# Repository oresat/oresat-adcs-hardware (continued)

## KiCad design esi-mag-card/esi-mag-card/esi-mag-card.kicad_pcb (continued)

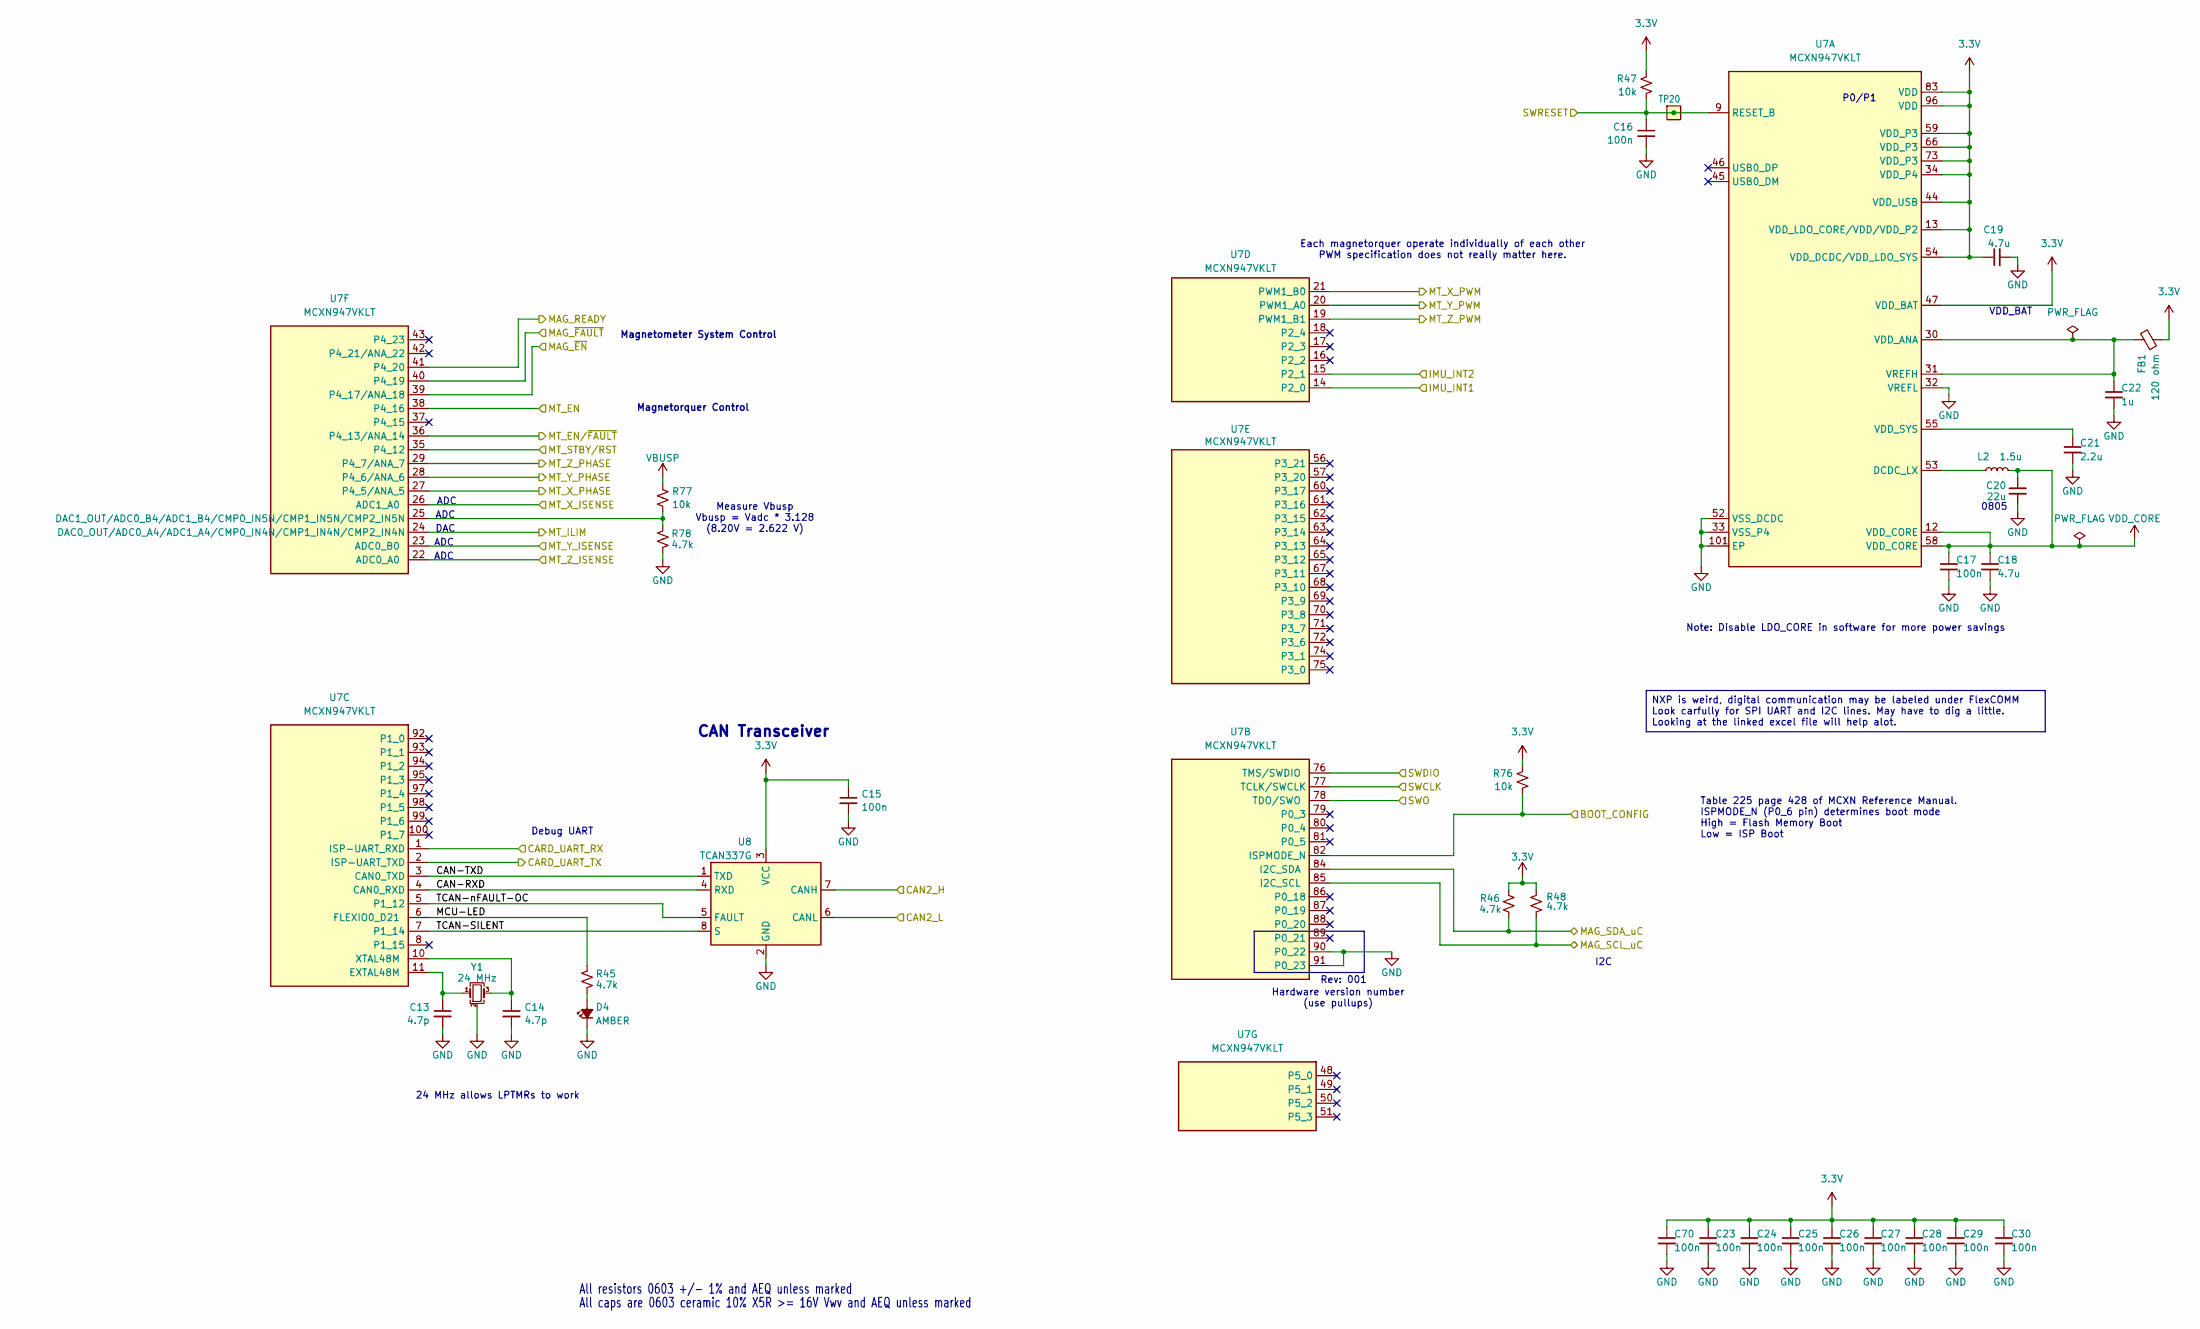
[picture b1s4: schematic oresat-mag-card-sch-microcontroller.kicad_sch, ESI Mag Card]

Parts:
C13, C14: 4.7p; 0603-C-NOSILK; MPN C0603C479D5GACAUTO
C15, C16, C17, C23, C24, C25, C26, C27, C28, C29, C30, C70: 100n; 0603-C-NOSILK; MPN C0603C104K5RACAUTO
C18, C19: 4.7u; 0603-C-NOSILK; MPN GRT188C71C475KE13D
C20: 22u; 0805-B-NOSILK; MPN GRT21BC81C226ME13L
C21: 2.2u; 0603-C-NOSILK; MPN GRT188C71E225KE13D
C22: 1u; 0603-C-NOSILK; MPN GRT188R71E105KE13D
D4: AMBER; LED_0603_1608Metric; MPN 150060AS75000
FB1: 120 ohm; 0805-B-NOSILK; MPN 2508051217Y6
L2: 1.5u; L_0805_2012Metric; MPN SRP2012TMA-1R5M
R45, R46, R48, R78: 4.7k; 0603-C-NOSILK; MPN RMCF0603FT4K70
R47, R76, R77: 10k; 0603-C-NOSILK; MPN RMCF0603FT10K0
TP20: Test-Point; TestPoint-0.75mm-th
U7: MCXN947VKLT; MCXN947KVLT-QFP50P1600X1600X160-101N; MPN MCXN947VKLT
U8: TCAN337G; SOT-23-8; MPN TCAN337GDCNR
Y1: 24 MHz; Crystal_SMD_2016-4Pin_2.0x1.6mm; MPN 830108212309

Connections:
3.3V: C15.1, C19.1, C23.1, C24.1, C25.1, C26.1, C27.1, C28.1, C29.1, C30.1, C70.1, FB1.1, R46.2, R47.2, R48.2, R76.2, U7.13 (VDD_LDO_CORE/VDD/VDD_P2), U7.34 (VDD_P4), U7.44 (VDD_USB), U7.47 (VDD_BAT), U7.54 (VDD_DCDC/VDD_LDO_SYS), U7.59 (VDD_P3), U7.66 (VDD_P3), U7.73 (VDD_P3), U7.83 (VDD), U7.96 (VDD), U8.3 (VCC); also elsewhere on the board
/CAN2_H: U8.7 (CANH); also elsewhere on the board
/CAN2_L: U8.6 (CANL); also elsewhere on the board
/Card Power Domain/BOOT_CONFIG: R76.1, U7.82 (ISPMODE_N); also elsewhere on the board
/Card Power Domain/CARD-UART-RX: U7.1 (ISP-UART_RXD); also elsewhere on the board
/Card Power Domain/CARD-UART-TX: U7.2 (ISP-UART_TXD); also elsewhere on the board
/Magnetometers + IMU/IMU_INT1: U7.14 (P2_0); also elsewhere on the board
/Magnetometers + IMU/IMU_INT2: U7.15 (P2_1); also elsewhere on the board
/Magnetometers + IMU/MAG_READY: U7.41 (P4_20); also elsewhere on the board
/Magnetometers + IMU/MAG_SCL_uC: R48.1, U7.85 (I2C_SCL); also elsewhere on the board
/Magnetometers + IMU/MAG_SDA_uC: R46.1, U7.84 (I2C_SDA); also elsewhere on the board
/Magnetometers + IMU/MAG_~EN: U7.39 (P4_17/ANA_18); also elsewhere on the board
/Magnetometers + IMU/MAG_~FAULT: U7.40 (P4_19); also elsewhere on the board
/Magnetorquers/MT_EN: U7.38 (P4_16); also elsewhere on the board
/Magnetorquers/MT_EN/~FAULT: U7.36 (P4_13/ANA_14); also elsewhere on the board
/Magnetorquers/MT_ILIM: U7.24 (DAC0_OUT/ADC0_A4/ADC1_A4/CMP0_IN4N/CMP1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); also elsewhere on the board
/Magnetorquers/MT_STBY/RST: U7.35 (P4_12); also elsewhere on the board
/Magnetorquers/MT_X_ISENSE: U7.26 (ADC1_A0); also elsewhere on the board
/Magnetorquers/MT_X_PHASE: U7.27 (P4_5/ANA_5); also elsewhere on the board
/Magnetorquers/MT_X_PWM: U7.21 (PWM1_B0); also elsewhere on the board
/Magnetorquers/MT_Y_ISENSE: U7.23 (ADC0_B0); also elsewhere on the board
/Magnetorquers/MT_Y_PHASE: U7.28 (P4_6/ANA_6); also elsewhere on the board
/Magnetorquers/MT_Y_PWM: U7.20 (PWM1_A0); also elsewhere on the board
/Magnetorquers/MT_Z_ISENSE: U7.22 (ADC0_A0); also elsewhere on the board
/Magnetorquers/MT_Z_PHASE: U7.29 (P4_7/ANA_7); also elsewhere on the board
/Magnetorquers/MT_Z_PWM: U7.19 (PWM1_B1); also elsewhere on the board
/Microcontroller/CAN-RXD: U7.4 (CAN0_RXD), U8.4 (RXD)
/Microcontroller/CAN-TXD: U7.3 (CAN0_TXD), U8.1 (TXD)
/Microcontroller/MCU-LED: R45.1, U7.6 (FLEXIO0_D21)
/Microcontroller/TCAN-SILENT: U7.7 (P1_14), U8.8 (S)
/Microcontroller/TCAN-nFAULT-OC: U7.5 (P1_12), U8.5 (FAULT)
/NRST: C16.1, R47.1, TP20.1 (1_1), U7.9 (RESET_B); also elsewhere on the board
/SWCLK: U7.77 (TCLK/SWCLK); also elsewhere on the board
/SWDIO: U7.76 (TMS/SWDIO); also elsewhere on the board
/SWO: U7.78 (TDO/SWO); also elsewhere on the board
GND: C13.2, C14.2, C15.2, C16.2, C17.2, C18.2, C19.2, C20.2, C21.2, C22.2, C23.2, C24.2, C25.2, C26.2, C27.2, C28.2, C29.2, C30.2, C70.2, D4.1 (K), R78.2, U7.32 (VREFL), U7.33 (VSS_P4), U7.52 (VSS_DCDC), U7.90 (P0_22), U7.91 (P0_23), U7.101 (EP), U8.2 (GND), Y1.2 (G), Y1.4 (G); also elsewhere on the board
unnamed: D4.2 (A), R45.2
unnamed: L2.2, U7.53 (DCDC_LX)
unnamed: C22.1, FB1.2, U7.30 (VDD_ANA), U7.31 (VREFH)
unnamed: C21.1, U7.55 (VDD_SYS)
unnamed: C14.1, U7.10 (XTAL48M), Y1.3
unnamed: C13.1, U7.11 (EXTAL48M), Y1.1
unnamed: R77.1, R78.1, U7.25 (DAC1_OUT/ADC0_B4/ADC1_B4/CMP0_IN5N/CMP1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)
VBUSP: R77.2; also elsewhere on the board
VDD_CORE: C17.1, C18.1, C20.1, L2.1, U7.12 (VDD_CORE), U7.58 (VDD_CORE)

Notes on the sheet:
Magnetometer System Control
Measure Vbusp Vbusp = Vadc * 3.128 (8.20V = 2.622 V)
Hardware version number (use pullups)
ADC
Magnetorquer Control
Each magnetorquer operate individually of each other PWM specification does not really matter here.
Debug UART
Note: Disable LDO_CORE in software for more power savings
0805
All resistors 0603 +/- 1% and AEQ unless marked
I2C
VDD_BAT
Table 225 page 428 of MCXN Reference Manual. ISPMODE_N (P0_6 pin) determines boot mode High = Flash Memory Boot Low = ISP Boot
CAN Transceiver
All caps are 0603 ceramic 10% X5R >= 16V Vwv and AEQ unless marked
24 MHz allows LPTMRs to work
P0/P1
DAC
Rev: 001
NXP is weird, digital communication may be labeled under FlexCOMM Look carfully for SPI UART and I2C lines. May have to dig a little. Looking at the linked excel file will help alot.

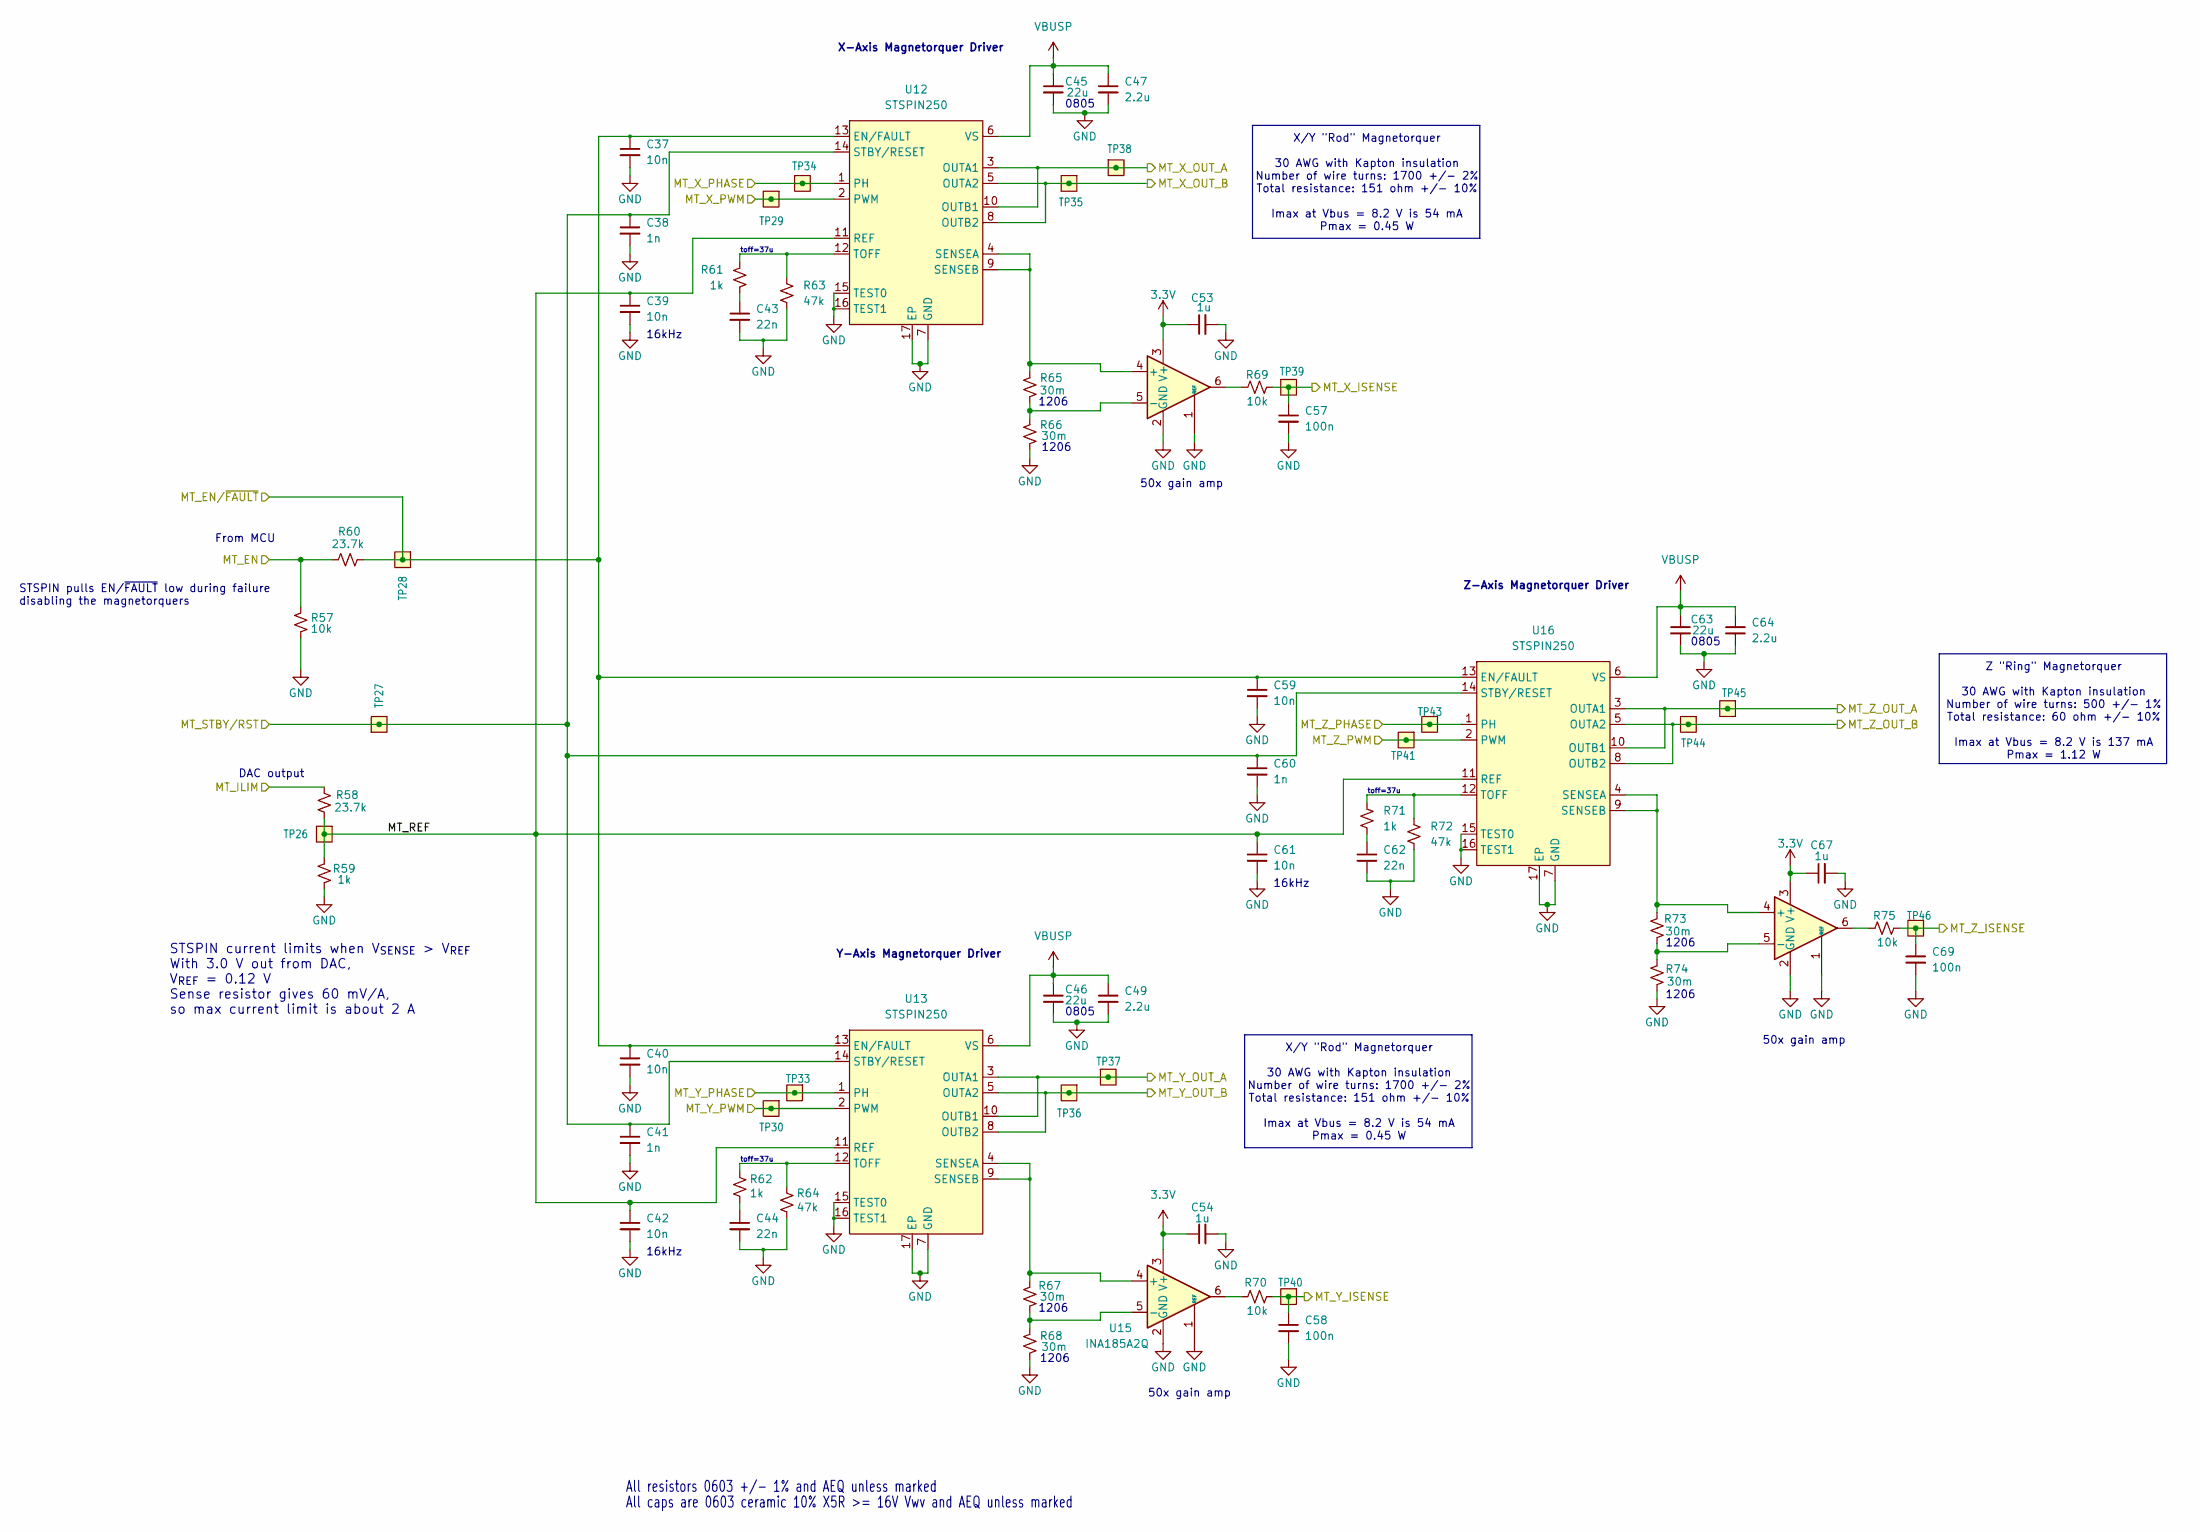
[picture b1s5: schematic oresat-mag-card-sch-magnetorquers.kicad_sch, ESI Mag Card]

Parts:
C37, C39, C40, C42, C59, C61: 10n; 0603-C-NOSILK; MPN C0603C103J5RACAUTO
C38, C41, C60: 1n; 0603-C-NOSILK; MPN C0603C102J5RACAUTO
C43, C44, C62: 22n; 0603-C-NOSILK; MPN C0603C223J5RACAUTO
C45, C46, C63: 22u; 0805-B-NOSILK; MPN GRT21BC81C226ME13L
C47, C49, C64: 2.2u; 0603-C-NOSILK; MPN GRT188C71E225KE13D
C53, C54, C67: 1u; 0603-C-NOSILK; MPN GRT188R71E105KE13D
C57, C58, C69: 100n; 0603-C-NOSILK; MPN C0603C104K5RACAUTO
R57, R69, R70, R75: 10k; 0603-C-NOSILK; MPN RMCF0603FT10K0
R58, R60: 23.7k; 0603-C-NOSILK; MPN RMCF0603FT23K7
R59, R61, R62, R71: 1k; 0603-C-NOSILK; MPN RMCF0603FT1K00
R63, R64, R72: 47k; 0603-C-NOSILK; MPN RMCF0603FT47K0
R65, R66, R67, R68, R73, R74: 30m; 1206-C; MPN CSR1206FK30L0
TP26, TP27, TP28, TP29, TP30, TP33, TP34, TP35, TP36, TP37, TP38, TP39, TP40, TP41, TP43, TP44, TP45, TP46: Test-Point; TestPoint-0.75mm-th
U12, U13, U16: STSPIN250; VQFN-16-1EP_3x3mm_P0.5mm_EP1.8x1.8mm; MPN STSPIN250
U14, U15, U17: INA185A2Q; SOT-363_SC-70-6; MPN INA185A2QDCKRQ1

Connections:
3.3V: C53.1, C54.1, C67.1, U14.3 (V+), U15.3 (V+), U17.3 (V+); also elsewhere on the board
/MT_X_OUT_A: TP38.1 (1_1), U12.3 (OUTA1), U12.10 (OUTB1); also elsewhere on the board
/MT_X_OUT_B: TP35.1 (1_1), U12.5 (OUTA2), U12.8 (OUTB2); also elsewhere on the board
/MT_Y_OUT_A: TP37.1 (1_1), U13.3 (OUTA1), U13.10 (OUTB1); also elsewhere on the board
/MT_Y_OUT_B: TP36.1 (1_1), U13.5 (OUTA2), U13.8 (OUTB2); also elsewhere on the board
/MT_Z_OUT_A: TP45.1 (1_1), U16.3 (OUTA1), U16.10 (OUTB1); also elsewhere on the board
/MT_Z_OUT_B: TP44.1 (1_1), U16.5 (OUTA2), U16.8 (OUTB2); also elsewhere on the board
/Magnetorquers/MT_EN: R57.2, R60.1; also elsewhere on the board
/Magnetorquers/MT_EN/~FAULT: C37.1, C40.1, C59.1, R60.2, TP28.1 (1_1), U12.13 (EN/FAULT), U13.13 (EN/FAULT), U16.13 (EN/FAULT); also elsewhere on the board
/Magnetorquers/MT_ILIM: R58.2; also elsewhere on the board
/Magnetorquers/MT_REF: C39.1, C42.1, C61.1, R58.1, R59.2, TP26.1 (1_1), U12.11 (REF), U13.11 (REF), U16.11 (REF)
/Magnetorquers/MT_STBY/RST: C38.1, C41.1, C60.1, TP27.1 (1_1), U12.14 (STBY/RESET), U13.14 (STBY/RESET), U16.14 (STBY/RESET); also elsewhere on the board
/Magnetorquers/MT_X_ISENSE: C57.1, R69.2, TP39.1 (1_1); also elsewhere on the board
/Magnetorquers/MT_X_PHASE: TP34.1 (1_1), U12.1 (PH); also elsewhere on the board
/Magnetorquers/MT_X_PWM: TP29.1 (1_1), U12.2 (PWM); also elsewhere on the board
/Magnetorquers/MT_Y_ISENSE: C58.1, R70.2, TP40.1 (1_1); also elsewhere on the board
/Magnetorquers/MT_Y_PHASE: TP33.1 (1_1), U13.1 (PH); also elsewhere on the board
/Magnetorquers/MT_Y_PWM: TP30.1 (1_1), U13.2 (PWM); also elsewhere on the board
/Magnetorquers/MT_Z_ISENSE: C69.1, R75.2, TP46.1 (1_1); also elsewhere on the board
/Magnetorquers/MT_Z_PHASE: TP43.1 (1_1), U16.1 (PH); also elsewhere on the board
/Magnetorquers/MT_Z_PWM: TP41.1 (1_1), U16.2 (PWM); also elsewhere on the board
GND: C37.2, C38.2, C39.2, C40.2, C41.2, C42.2, C43.2, C44.2, C45.2, C46.2, C47.2, C49.2, C53.2, C54.2, C57.2, C58.2, C59.2, C60.2, C61.2, C62.2, C63.2, C64.2, C67.2, C69.2, R57.1, R59.1, R63.2, R64.2, R66.1, R68.1, R72.2, R74.1, U12.7 (GND), U12.15 (TEST0), U12.16 (TEST1), U12.17 (EP), U13.7 (GND), U13.15 (TEST0), U13.16 (TEST1), U13.17 (EP), U14.1 (REF), U14.2 (GND), U15.1 (REF), U15.2 (GND), U16.7 (GND), U16.15 (TEST0), U16.16 (TEST1), U16.17 (EP), U17.1 (REF), U17.2 (GND); also elsewhere on the board
unnamed: C43.1, R61.2
unnamed: C44.1, R62.2
unnamed: C62.1, R71.2
unnamed: R69.1, U14.6
unnamed: R70.1, U15.6
unnamed: R75.1, U17.6
unnamed: R65.2, U12.4 (SENSEA), U12.9 (SENSEB), U14.4 (+)
unnamed: R61.1, R63.1, U12.12 (TOFF)
unnamed: R67.2, U13.4 (SENSEA), U13.9 (SENSEB), U15.4 (+)
unnamed: R62.1, R64.1, U13.12 (TOFF)
unnamed: R65.1, R66.2, U14.5 (-)
unnamed: R67.1, R68.2, U15.5 (-)
unnamed: R73.2, U16.4 (SENSEA), U16.9 (SENSEB), U17.4 (+)
unnamed: R71.1, R72.1, U16.12 (TOFF)
unnamed: R73.1, R74.2, U17.5 (-)
VBUSP: C45.1, C46.1, C47.1, C49.1, C63.1, C64.1, U12.6 (VS), U13.6 (VS), U16.6 (VS); also elsewhere on the board

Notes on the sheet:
1206
STSPIN current limits when V_{SENSE} > V_{REF} With 3.0 V out from DAC, V_{REF} = 0.12 V Sense resistor gives 60 mV/A, so max current limit is about 2 A
DAC output
16kHz
50x gain amp
toff=37u
Y-Axis Magnetorquer Driver
X/Y "Rod" Magnetorquer 30 AWG with Kapton insulation Number of wire turns: 1700 +/- 2% Total resistance: 151 ohm +/- 10% Imax at Vbus = 8.2 V is 54 mA Pmax = 0.45 W
From MCU
All caps are 0603 ceramic 10% X5R >= 16V Vwv and AEQ unless marked
Z "Ring" Magnetorquer 30 AWG with Kapton insulation Number of wire turns: 500 +/- 1% Total resistance: 60 ohm +/- 10% Imax at Vbus = 8.2 V is 137 mA Pmax = 1.12 W
0805
STSPIN pulls EN/~{FAULT} low during failure disabling the magnetorquers
All resistors 0603 +/- 1% and AEQ unless marked
Z-Axis Magnetorquer Driver
X-Axis Magnetorquer Driver

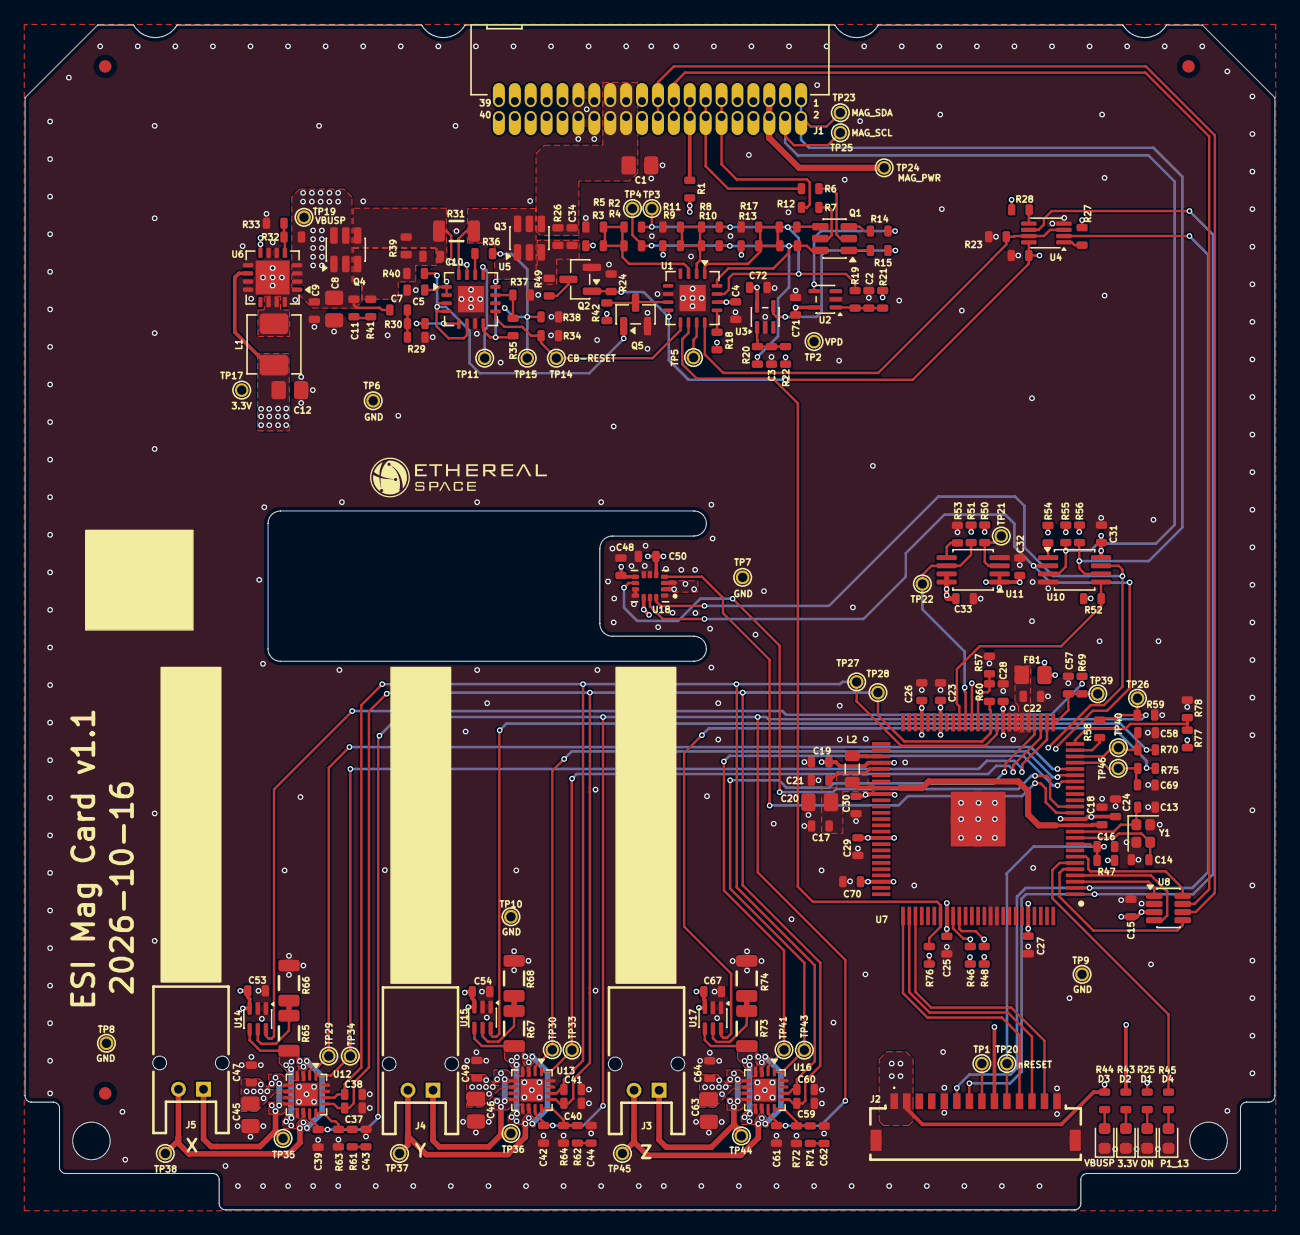
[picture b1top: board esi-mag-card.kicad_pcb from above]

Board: 4 copper layers, 99.8 x 94.6 mm, 219 parts (0 on the bottom side), 120 nets.

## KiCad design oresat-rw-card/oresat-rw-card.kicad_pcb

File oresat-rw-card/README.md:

---
title: "**OreSat Reaction Wheel (RW) Card**"
subtitle: |
  **Fabrication and Assembly Information**\
  For build TIME-STAMP
fontsize: 10pt
geometry:
  - margin=0.5in
toc: true
toc-depth: 2
colorlinks: true
urlcolor: blue
---

\newpage

# About this Board

## Board Description

The OreSat RW Card run the four reaction wheels on the open source [OreSat CubeSat system](https://www.oresat.org/). The RW card:

- Has an OreSat Power Domain (OPD) per reaction wheel.
- Requires a flexible cable between the card and the RW board.

## Documentation Links

- RW card hardware Git repository: <https://github.com/oresat/oresat-adcs-hardware>
- **TODO:** RW card Design Notes + Design Review Notes

## Documentation Files

| Filename                        | Notes                                    |
| ------------------------------- | ---------------------------------------- |
| README.pdf                      | This README file                         |
| PROJECT-NAME-outline.dxf        | Board outline (with holes) in DXF format |
| PROJECT-NAME-pcba.step          | 3D model of PCBA (with components)       |
| PROJECT-NAME-render-bot.jpg     | Render of the top of the 3D model        |
| PROJECT-NAME-render-bot.jpg     | Render of the bottom of the 3D model     |
| PROJECT-NAME-schematic.pdf      | PDF of board schematics                  |

## Contact Information

- Website: <https://www.oresat.org/>
- Email: <oresat@pdx.edu>
- Instagram: @pdxaerospace

## Board Renders

{width=50%}
{width=50%}

\newpage

# Printed Circuit Board (PCB) Fabrication Information

## Board Info

- 4 layer board
- Bounding box is 99.8 x 94.6 mm (3.93 x 3.72 in)
- Board thickness is 1.59 mm (0.063 inch)

## Board Requirements

- Design Rules
    - Minimum Trace / Space design rules
       - Outer layers: 0.127 mm (5.0 mil) / 0.127 mm (5.0 mil)
       - Inner layers: 0.127 mm (5.0 mil) / 0.127 mm (5.0 mil)
    - Outer dimension router tolerance: +/- 0.254 mm (10.0 mil)
    - Hole placement tolerance: +/- 0.075 mm (3.0 mil)
    - Inner tab routed slot tolerance: +/- 0.254 mm (10.0 mil)
- Drills
   - Drill Positional Tolerance: 0.051 mm (2.0 mil)
   - Drill Size tolerance: +/- 0.064 mm (2.5 mil)
- Plated/Un-plated holes
  - There are 2 un-plated (NPT) holes
  - There are 664 plated through (PTH) holes
  - PTH minimum diameter: 0.254 mm (10 mil)
  - PTH minimum annulus: 0.102 mm (4 mil) radius
- Outline/Routing
  - Requires a 1.0 mm or smaller diameter routing bit
- Slots
  - There is one cutout.
- Cutouts
  - There are no cutouts
- There are 3 fiducials on the top layer and 3 fiducials on the bottom layer.
- Panel tabs ("mouse bites")
   - Card edges must be smooth; no mouse bites or other intrusions into the card outline.
   - If external mouse bites are required, minimize and customer will remove by hand before assembly.
- If not otherwise specified, build to IPC 6012 Class 2 or better.

## Materials

- No controlled impedance.
- Outer layers must be 1 oz Copper, inner layers can be 0.5 or 1.0 oz Copper.
- Isola FR408HR or material recommended.
- Board Surface treatment should be ENIG, althogh immersion Silver is acceptable.
- White silkscreen on top and bottom surface
- Taiyo PSR-4000 or equivalent soldermask on top and bottom, no requirements for color.

## Suggested Stack Up

| Layer         | Thickness           | Notes                                        |
|---------------|---------------------|----------------------------------------------|
| Top Copper    | 0.043 mm /  1.7 mil |  Layer 1 foil, 1 oz Cu after plating         |
| prepreg       | 0.200 mm /  7.9 mil |  Prepreg - Isola FR408HR 2113                |
| Layer 2       | 0.018 mm /  0.7 mil |  Layer 2 foil, 0.5 oz Cu                     |
| Core          | 0.991 mm /   39 mil |  Core Isola FR408HR                          |
| Layer 3       | 0.018 mm /  0.7 mil |  Layer 3 foil, 0.5 oz Cu                     |
| prepreg       | 0.200 mm /  7.9 mil |  Prepreg - Isola FR408HR 2113                |
| Bottom Copper | 0.043 mm /  1.7 mil |  Layer 4 foil, 1 oz copper after plating     |
| **Total Stackup** | **1.588 mm / 62.5 mil** |                                      |

## Array / Panel Information

- Coordinate with Contract Manufacturer (CM) for optimal size of this panel.
- If no feedback from CM, then produce single boards (no panel).

## Fabrication Files

### IPC-2581 File

| Filename                 | Notes                                   |
| ------------------------ | --------------------------------------- |
| PROJECT-NAME-ipc2581.xml | IPC-2581 board information file         |

### Legacy PCB Files

| Filename                      | Notes                                         |
| ------------------------------| --------------------------------------------- |
| PROJECT-NAME-Edge_Cuts.gbr    | RS274X file for the dimension (outline) layer |
| PROJECT-NAME-F_Silkscreen.gbr | RS274X file for the top silkscreen            |
| PROJECT-NAME-F_Mask.gbr       | RS274X file for the top soldermask            |
| PROJECT-NAME-F_Cu.gbr         | RS274X file for the top copper layer          |
| PROJECT-NAME-In1_Cu.gbr       | RS274X file for the layer 2 copper            |
| PROJECT-NAME-In2_Cu.gbr       | RS274X file for the layer 3 copper            |
| PROJECT-NAME-B_Cu.gbr         | RS274X file for the bottom copper layer       |
| PROJECT-NAME-B_Mask.gbr       | RS274X file for the bottom soldermask         |
| PROJECT-NAME-B_Silkscreen.gbr | RS274X file for the bottom silkscreen         |
| PROJECT-NAME-NPTH.drl         | Excellon file for non-plated through holes    |
| PROJECT-NAME-PTH.drl          | Excellon file for plated through holes        | 

\newpage

# Printed Circuit Board Assembly (PCBA) Information

## Assembly Info

- There are components on the top and bottom sides of the board.
- This PCBA is mostly surface mount (SMT) with a one through-hole (THT) components.

## Assembly Requirements

- Assemble to IPC Class 2 or better
- Bake components that are not moisture sealed to appropriate levels as required.
- Solder paste MUST be leaded.
- Aqueous flux and wash strongly preferred.
   - Clean to NASA Standard "Visibly Clean (VC)": No particles or residues are visible to the naked eye.
- No conformal coating.
- Ship in antistatic protective bag

## Component Specific Assembly Information

- No specific requirements.

## Assembly Files

### IPC-2581 File

| Filename                 | Notes                           |
| ------------------------ | ------------------------------- |
| PROJECT-NAME-ipc2581.xml | IPC-2581 board information file |

### Bill of Materials (BOM)

| Filename             | Description                            |
| -------------------- | -------------------------------------- |
| PROJECT-NAME-bom.csv | BOM in Comma Separated Variable format |

### Solder Paste Stencils

| Filename                 | Notes                                            |
| ------------------------ | ------------------------------------------------ |
| PROJECT-NAME-B_Paste.gbr | RS274X file for top/front solder paste stencil   |
| PROJECT-NAME-F_Paste.gbr | RS274X file for bottom/back solder paste stencil |

### Mounting/Placement Location

| Filename            | Description                                 |
| ------------------- | ------------------------------------------- |
| PROJECT-NAME-3u.pos | Pick and place locations for components     |

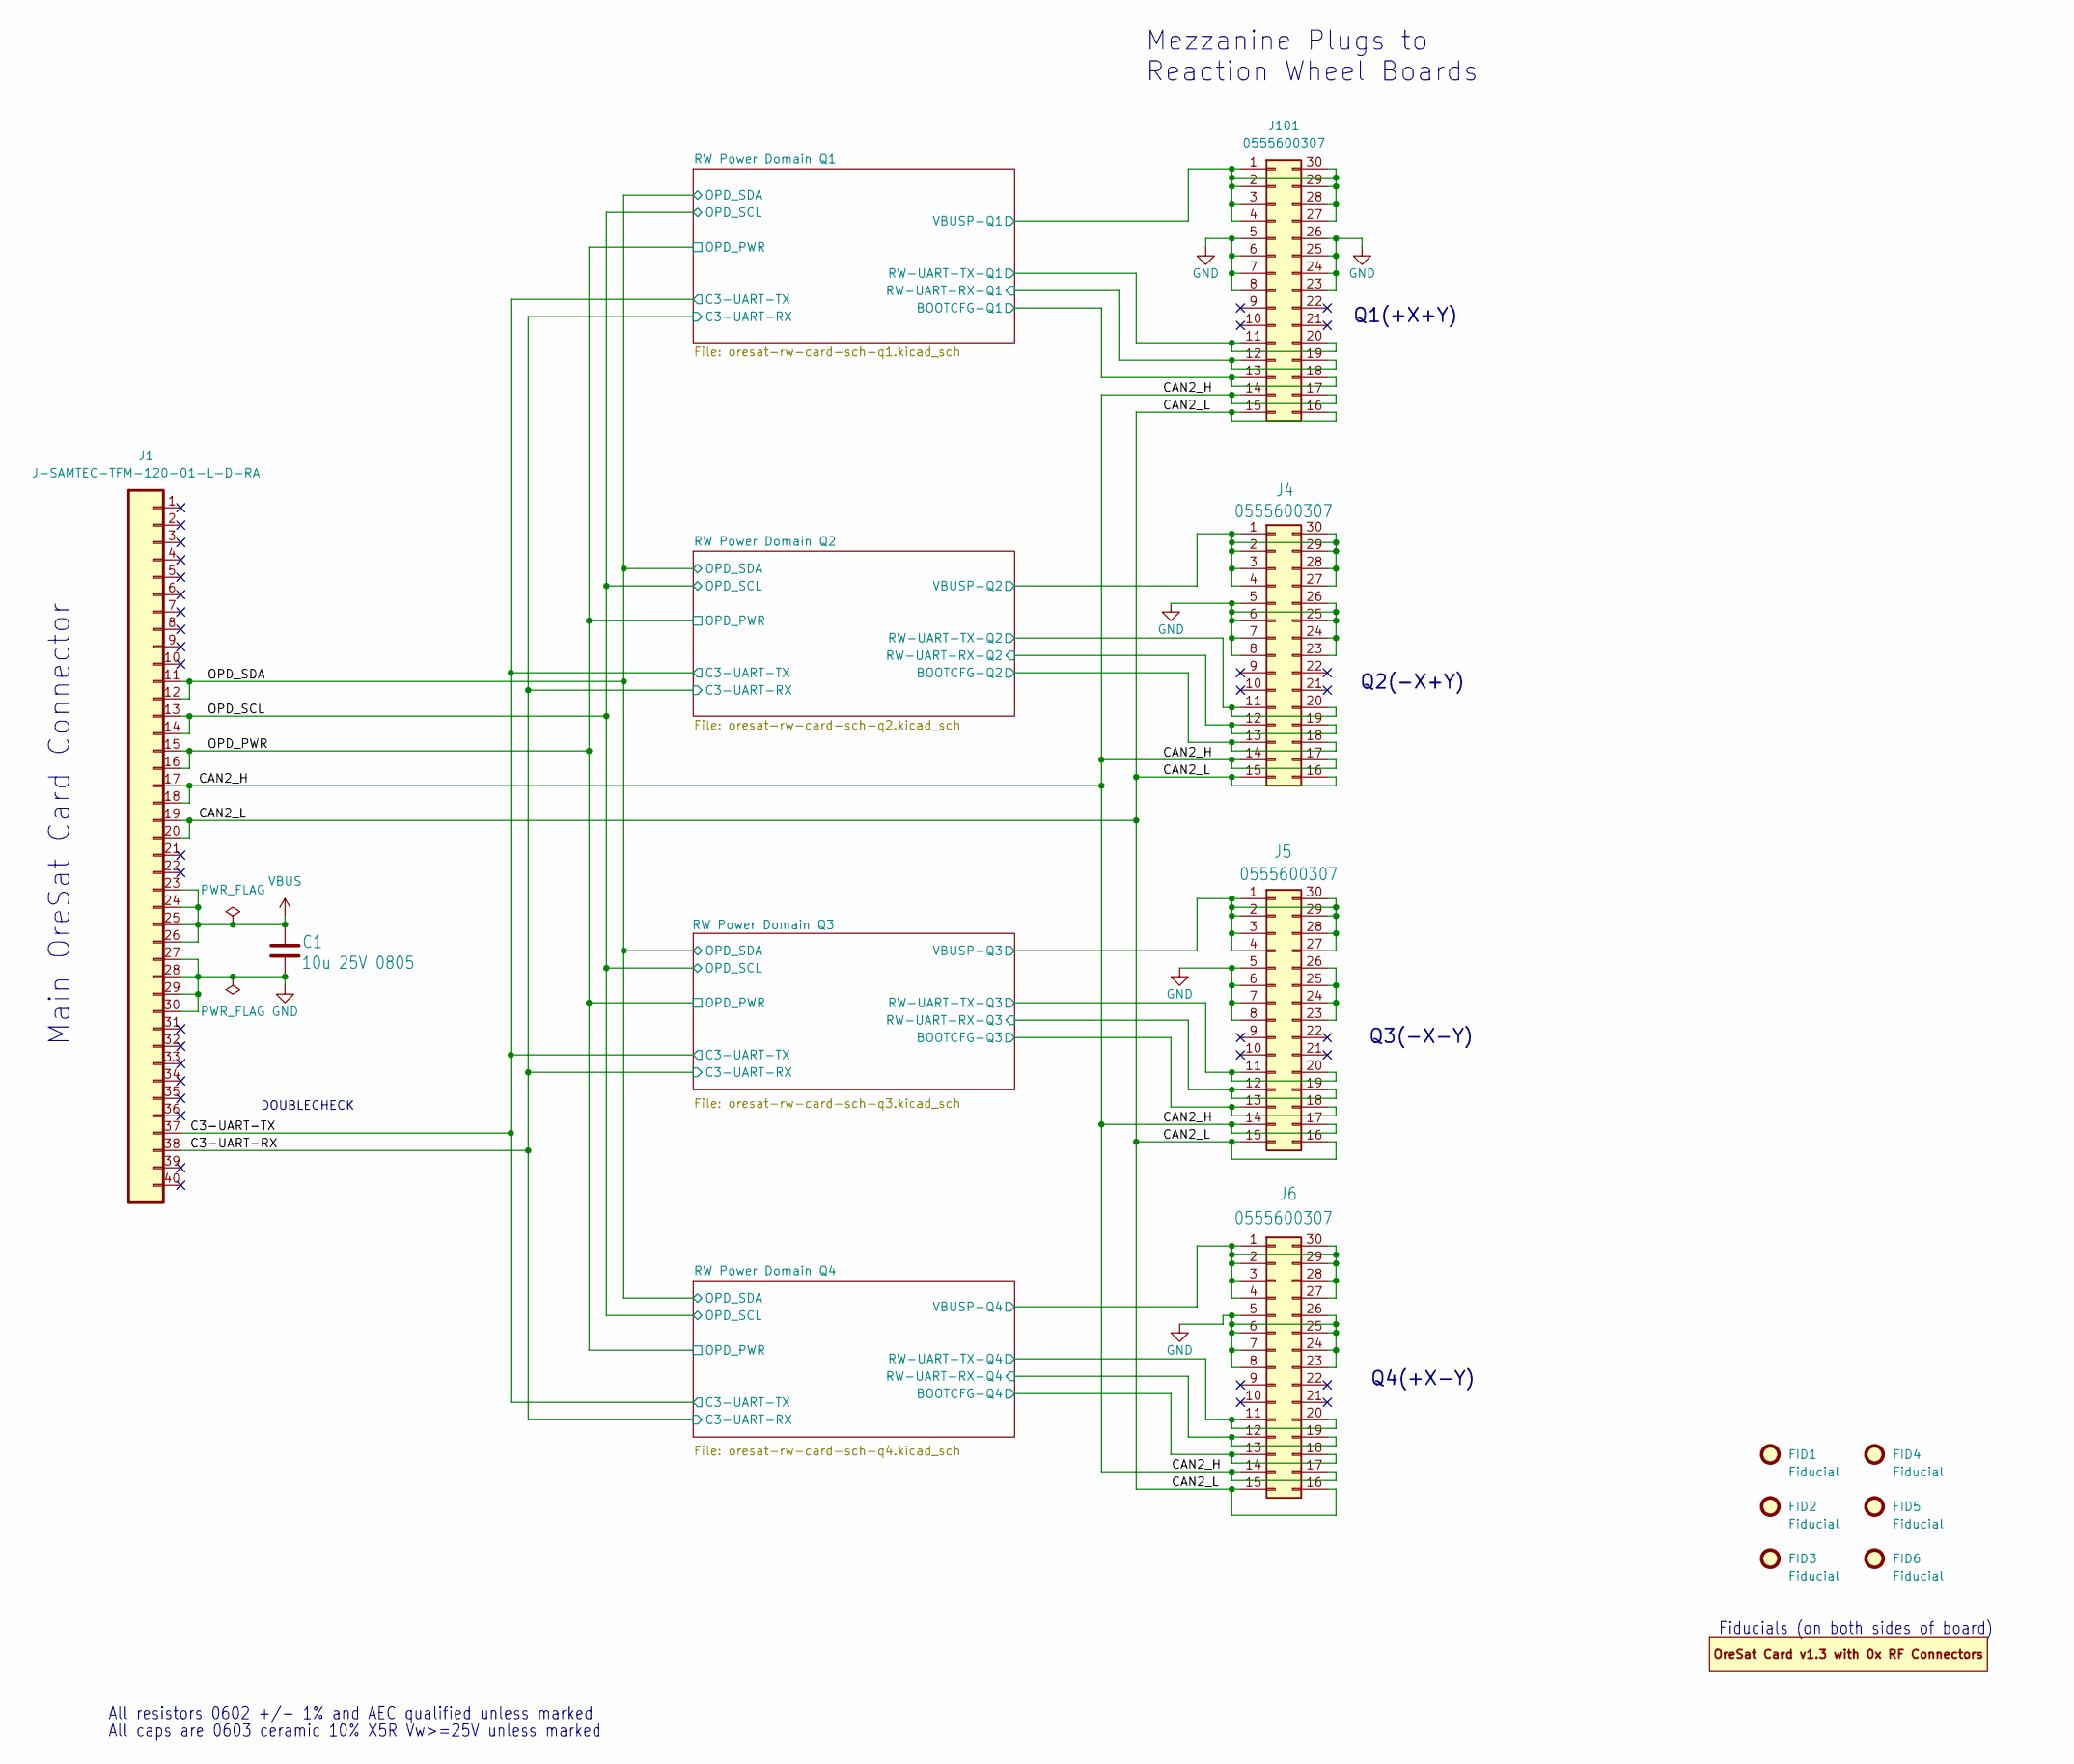
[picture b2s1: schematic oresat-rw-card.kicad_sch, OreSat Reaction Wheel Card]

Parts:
C1: 10u 25V 0805; C_0805_2012Metric; MPN GRT21BC71E106KE13K
FID1, FID2, FID3, FID4, FID5, FID6: Fiducial; Fiducial_1mm_Mask2mm
J1: J-SAMTEC-TFM-120-01-L-D-RA; J-SAMTEC-TFM-120-X1-XXX-D-RA; MPN TFM-120-01-L-D-RA
J4, J5, J6, J101: 0555600307; J-MOLEX-555600307; MPN 0555600307
PCB1: ORESAT-CARD-V1.3-GENERIC-0RF; ORESAT-CARD-V1.3-0RF

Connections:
/C3-UART-RX: J1.38; also elsewhere on the board
/C3-UART-TX: J1.37; also elsewhere on the board
/CAN2_H: J1.17, J1.18, J4.14, J4.17, J5.14, J5.17, J6.14, J6.17, J101.14, J101.17
/CAN2_L: J1.19, J1.20, J4.15, J4.16, J5.15, J5.16, J6.15, J6.16, J101.15, J101.16
/OPD_PWR: J1.15, J1.16; also elsewhere on the board
/OPD_SCL: J1.13, J1.14; also elsewhere on the board
/OPD_SDA: J1.11, J1.12; also elsewhere on the board
/RW Power Domain Q1/BOOTCFG-Q1: J101.13, J101.18; also elsewhere on the board
/RW Power Domain Q1/RW-UART-RX-Q1: J101.12, J101.19; also elsewhere on the board
/RW Power Domain Q1/RW-UART-TX-Q1: J101.11, J101.20; also elsewhere on the board
/RW Power Domain Q1/VBUSP-Q1: J101.1, J101.2, J101.3, J101.4, J101.27, J101.28, J101.29, J101.30; also elsewhere on the board
/RW Power Domain Q2/BOOTCFG-Q2: J4.13, J4.18; also elsewhere on the board
/RW Power Domain Q2/RW-UART-RX-Q2: J4.12, J4.19; also elsewhere on the board
/RW Power Domain Q2/RW-UART-TX-Q2: J4.11, J4.20; also elsewhere on the board
/RW Power Domain Q2/VBUSP-Q2: J4.1, J4.2, J4.3, J4.4, J4.27, J4.28, J4.29, J4.30; also elsewhere on the board
/RW Power Domain Q3/BOOTCFG-Q3: J5.13, J5.18; also elsewhere on the board
/RW Power Domain Q3/RW-UART-RX-Q3: J5.12, J5.19; also elsewhere on the board
/RW Power Domain Q3/RW-UART-TX-Q3: J5.11, J5.20; also elsewhere on the board
/RW Power Domain Q3/VBUSP-Q3: J5.1, J5.2, J5.3, J5.4, J5.27, J5.28, J5.29, J5.30; also elsewhere on the board
/RW Power Domain Q4/BOOTCFG-Q4: J6.13, J6.18; also elsewhere on the board
/RW Power Domain Q4/RW-UART-RX-Q4: J6.12, J6.19; also elsewhere on the board
/RW Power Domain Q4/RW-UART-TX-Q4: J6.11, J6.20; also elsewhere on the board
/RW Power Domain Q4/VBUSP-Q4: J6.1, J6.2, J6.3, J6.4, J6.27, J6.28, J6.29, J6.30; also elsewhere on the board
GND: C1.2, J1.27, J1.28, J1.29, J1.30, J4.5, J4.6, J4.7, J4.8, J4.23, J4.24, J4.25, J4.26, J5.5, J5.6, J5.7, J5.8, J6.5, J6.6, J6.7, J6.8, J6.23, J6.24, J6.25, J6.26, J101.5, J101.6, J101.7, J101.8, J101.23, J101.24, J101.25, J101.26; also elsewhere on the board
unnamed: J5.23, J5.24, J5.25, J5.26
VBUS: C1.1, J1.23, J1.24, J1.25, J1.26; also elsewhere on the board

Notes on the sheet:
Q3(-X-Y)
Main OreSat Card Connector
DOUBLECHECK
Fiducials (on both sides of board)
Q4(+X-Y)
All caps are 0603 ceramic 10% X5R Vw>=25V unless marked
Q2(-X+Y)
Q1(+X+Y)
All resistors 0602 +/- 1% and AEC qualified unless marked
Mezzanine Plugs to Reaction Wheel Boards
